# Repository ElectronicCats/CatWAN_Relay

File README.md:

# CatWAN Relay

Are you interested in applying LoRa in an industrial environment or even connect a CNC or a PLC as well to a LoRaWAN network? 

This board allows you to communicate with every LoRa device which works in the 915 Mhz band.

In this board you will find 3 relays outputs and 3 opto-isolated inputs, and it can be powered from 12v to 24v with a on/off jumper.

By now the provided firmware works as an invisible way to connect two wireless relays based on interrupts, this board its compatible with the [Arduino LoRa library](https://github.com/sandeepmistry/arduino-LoRa) from @sandeepmistry but it can work with the [Radio Head library](https://www.airspayce.com/mikem/arduino/RadioHead/) this using only the LoRa radio if you want to use LoRaWAN you should use the [Arduino LMIC](https://github.com/matthijskooijman/arduino-lmic/tree/non-avr-printf).

This device can work in networks LoRaWAN compatible with classes A, B and C, although we currently do not have a firmware for this way of working. The CatWAN Relay firmware is completely open source and you can find it in our repository along with the schematic. If you want to reprogram this device you can do it through Arduino IDE and its USB port or if you do not have to use a J-Link. ATMEL-ICE or a DIY SWD programmer

This device has a SAMD21 ARM Cortex microcontroller at 48Mhz with native USB 2.1, with 256Kb for programming, compatible with Arduino and Circuit Python.

Check [our repository](https://github.com/ElectronicCats/Arduino_Boards_Index) for Arduino IDE more details and software downloads!

Designed by Electronic Cats.
# License 

Firmware released under an GNU AGPL v3.0 license. See the LICENSE file for more information.

Hardware released under an CERN Open Hardware Licence v1.2. See the LICENSE_HARDWARE file for more information.

Electronic Cats is a registered trademark, please do not use if you sell these PCBs.

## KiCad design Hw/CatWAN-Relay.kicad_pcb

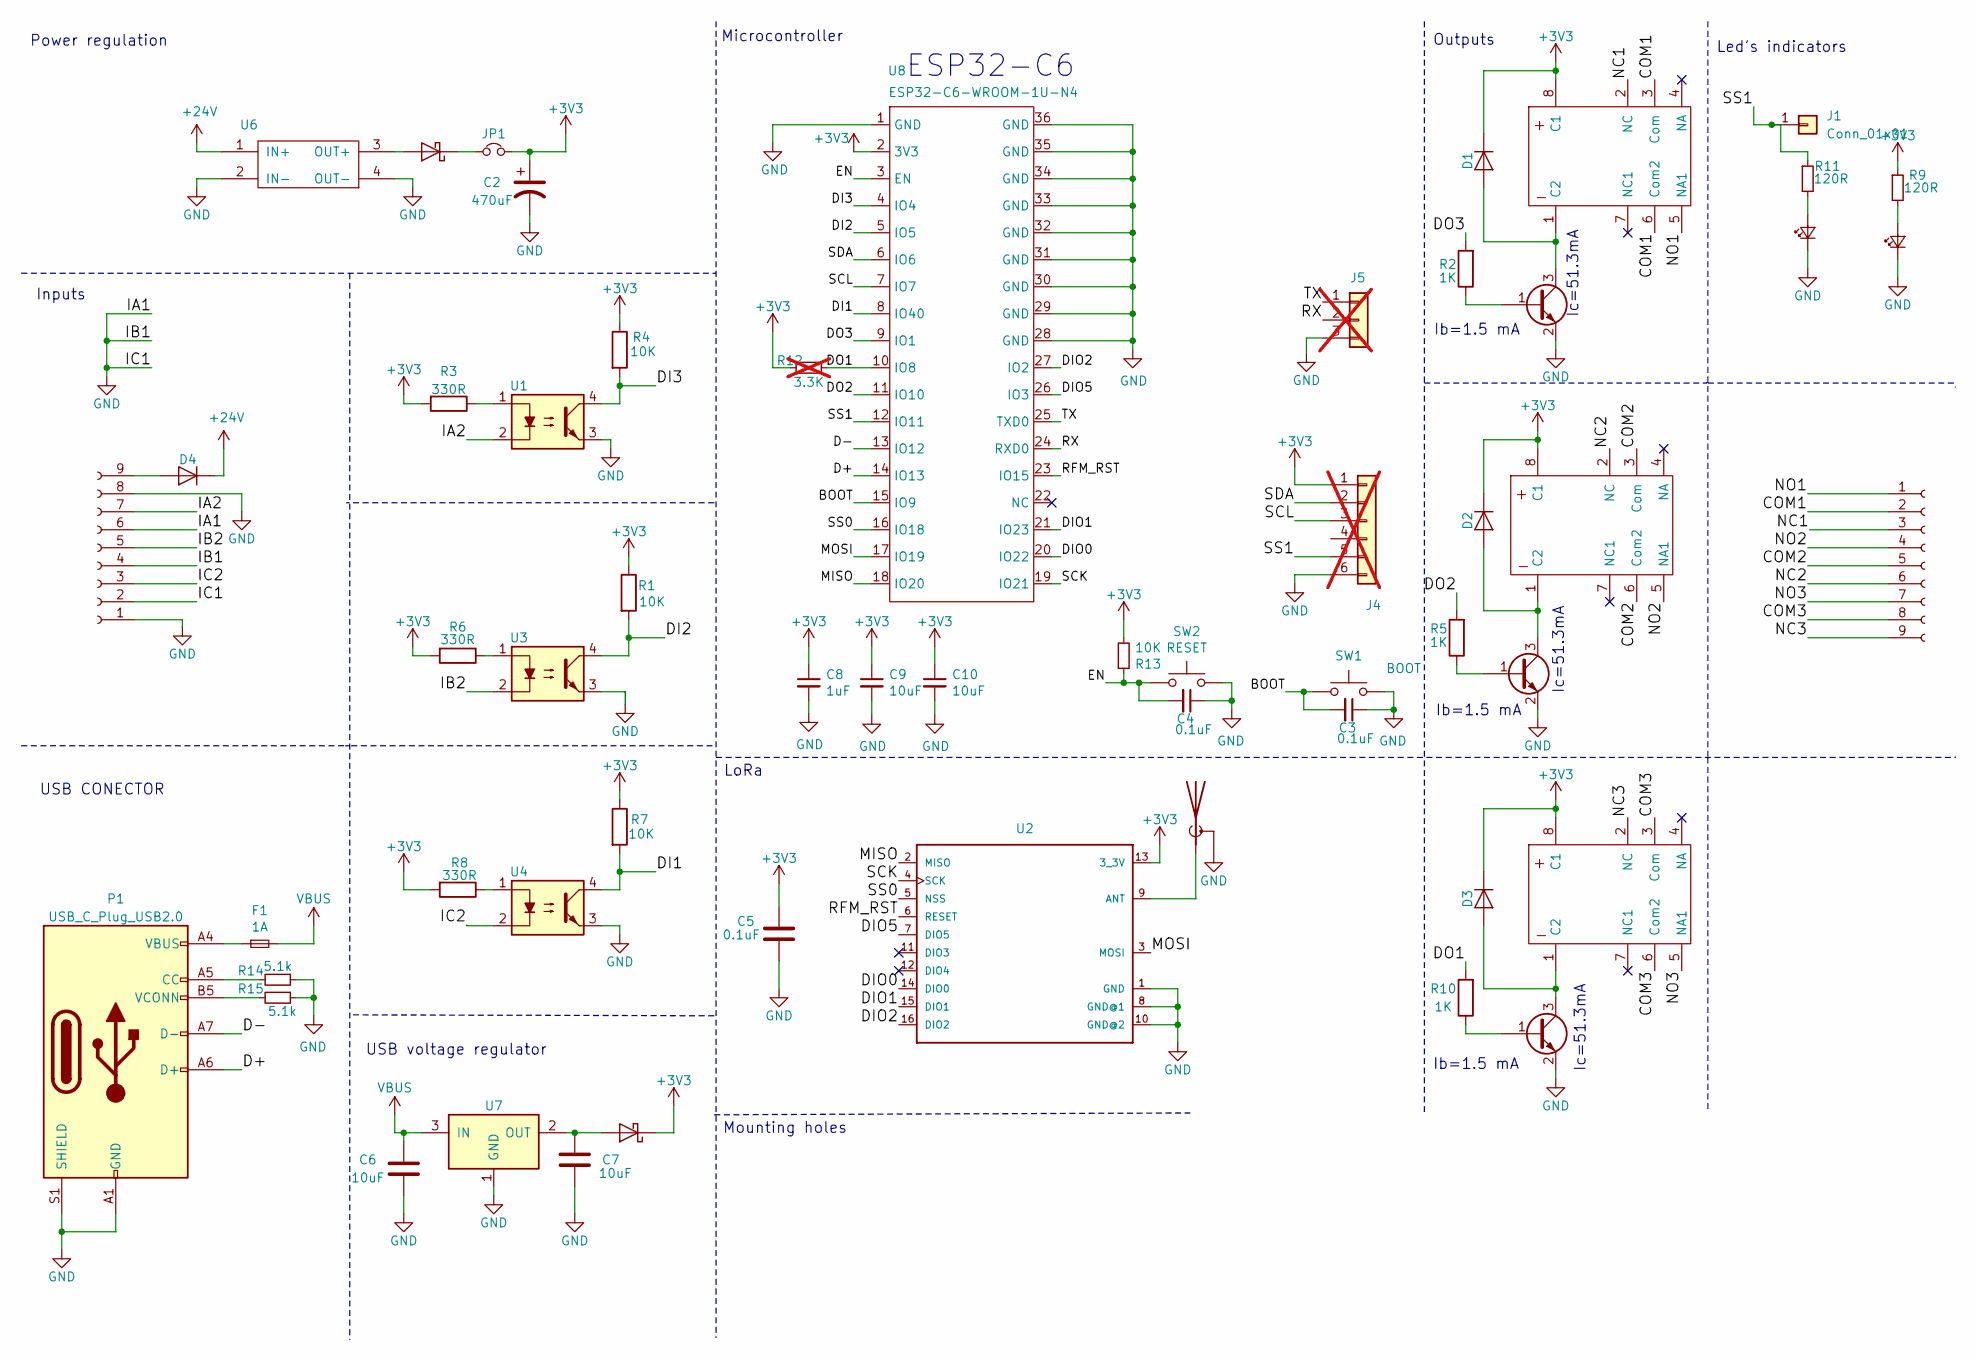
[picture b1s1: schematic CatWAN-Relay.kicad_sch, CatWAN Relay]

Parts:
AE1: Antenna_Shield; U.FL_Molex_MCRF_73412-0110_Vertical; LCSC# C7426714
C2: 470uF; C_Elec_6.3x7.7; LCSC# C5354997
C3, C4, C5: 0.1uF; C_0603_1608Metric; LCSC# C15725
C6, C7, C9, C10: 10uF; C_0603_1608Metric; LCSC# C85713
C8: 1uF; C_0603_1608Metric; LCSC# C15849
D1, D2, D3, D4: SOD4007-MS; D_SOD-123F; LCSC# C3008061
D5, D8: MBR120; D_SOD-123; LCSC# C130880
D6: ON; LED_0805_2012Metric_Pad1.15x1.40mm_HandSolder; LCSC# C130114
D7: SS0_LED; LED_0805_2012Metric_Pad1.15x1.40mm_HandSolder; LCSC# C130114
F1: 1A; Fuse_0603_1608Metric; LCSC# C151139
J1: Conn_01x01; PinHeader_1x01_P2.54mm_Vertical
J2: INPUTS; TerminalBlock_Phoenix_MKDS-1,5-9-5.08_1x09_P5.08mm_Horizont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
J3: OUTPUTS; TerminalBlock_Phoenix_MKDS-1,5-9-5.08_1x09_P5.08mm_Horizont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
J4: I2C; PinHeader_1x06_P2.54mm_Vertical; not fitted
J5: Serial; PinHeader_1x03_P2.54mm_Vertical; not fitted
JP1: ADJ; PinHeader_1x02_P2.54mm_Vertical
P1: USB_C_Plug_USB2.0; C393939; LCSC# C393939
Q1, Q2, Q3: MMBT2222A; SOT-23; LCSC# C916372
R1, R4, R7, R13: 10K; R_0603_1608Metric; LCSC# C15401
R2, R5, R10: 1K; R_0603_1608Metric; LCSC# C115325
R3, R6, R8: 330R; R_0603_1608Metric; LCSC# C25231
R9, R11: 120R; R_0603_1608Metric; LCSC# C22787
R12: 3.3K; R_0603_1608Metric; not fitted
R14, R15: 5.1k; R_0603_1608Metric; LCSC# C122969
SW1: BOOT; SW_Push_SPST_NO_Alps_SKRK; LCSC# C455281
SW2: RESET; SW_Push_SPST_NO_Alps_SKRK; LCSC# C455281
U1, U3, U4: AT3H7C-CuH-S; SOP-4_4.4x2.6mm_P1.27mm; LCSC# C20612661
U2: RFM95W-915-868; RFM95W
U6: LM2596_DC-DC; LM2596DC-DC
U7: AP2114H-3.3TRG1; SOT-223-3_TabPin2; LCSC# C150716
U8: ESP32-C6-WROOM-1U-N4; ESP32-C6-WROOM-1U
Y1, Y2, Y3: UD2-3NU; LCSC# C90259

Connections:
+3V3: C2.1, C5.1, C8.1, C9.1, C10.1, D1.1 (K), D2.1 (K), D3.1 (K), D5.1 (K), J4.1, JP1.2, R1.1, R3.2, R4.1, R6.2, R7.1, R8.2, R9.1, R12.2, R13.2, U2.13 (3_3V), U8.2 (3V3), Y1.8 (C1), Y2.8 (C1), Y3.8 (C1)
+24V: D4.1 (K), U6.1 (IN+)
/<NO NET>: J4.4
/BOOT: C3.2, SW1.2, U8.15 (IO9)
/COM1: J3.2, Y1.3 (Com), Y1.6 (Com2)
/COM2: J3.5, Y2.3 (Com), Y2.6 (Com2)
/COM3: J3.8, Y3.3 (Com), Y3.6 (Com2)
/D+: P1.A6 (D+), U8.14 (IO13)
/D-: P1.A7 (D-), U8.13 (IO12)
/DI1: R7.2, U4.4, U8.8 (IO40)
/DI2: R1.2, U3.4, U8.5 (IO5)
/DI3: R4.2, U1.4, U8.4 (IO4)
/DIO0: U2.14 (DIO0), U8.20 (IO22)
/DIO1: U2.15 (DIO1), U8.21 (IO23)
/DIO2: U2.16 (DIO2), U8.27 (IO2)
/DIO5: U2.7 (DIO5), U8.26 (IO3)
/DO1: R10.2, R12.1, U8.10 (IO8)
/DO2: R5.2, U8.11 (IO10)
/DO3: R2.2, U8.9 (IO1)
/EN: C4.2, R13.1, SW2.2, U8.3 (EN)
/IA2: J2.7, U1.2
/IB2: J2.5, U3.2
/IC2: J2.3, U4.2
/MISO: U2.2 (MISO), U8.18 (IO20)
/MOSI: U2.3 (MOSI), U8.17 (IO19)
/NC1: J3.3, Y1.2 (NC)
/NC2: J3.6, Y2.2 (NC)
/NC3: J3.9, Y3.2 (NC)
/NO1: J3.1, Y1.5 (NA1)
/NO2: J3.4, Y2.5 (NA1)
/NO3: J3.7, Y3.5 (NA1)
/RFM_RST: U2.6 (RESET), U8.23 (IO15)
/RX: J5.2, U8.24 (RXD0)
/SCK: U2.4 (SCK), U8.19 (IO21)
/SCL: J4.3, U8.7 (IO7)
/SDA: J4.2, U8.6 (IO6)
/SS0: U2.5 (NSS), U8.16 (IO18)
/SS1: J1.1, J4.5, R11.1, U8.12 (IO11)
/TX: J5.1, U8.25 (TXD0)
GND: AE1.2 (Shield), C2.2, C3.1, C4.1, C5.2, C6.2, C7.2, C8.2, C9.2, C10.2, D6.1 (K), D7.1 (K), J2.1, J2.2, J2.4, J2.6, J2.8, J4.6, J5.3, P1.A1 (GND), P1.A12 (GND), P1.B1 (GND), P1.B12 (GND), P1.S1 (SHIELD), Q1.2 (E), Q2.2 (E), Q3.2 (E), R14.1, R15.1, SW1.1, SW2.1, U1.3, U2.1 (GND), U2.8 (GND@1), U2.10 (GND@2), U3.3, U4.3, U6.2 (IN-), U6.4 (OUT-), U7.1 (GND), U8.1 (GND), U8.28 (GND), U8.29 (GND), U8.30 (GND), U8.31 (GND), U8.32 (GND), U8.33 (GND), U8.34 (GND), U8.35 (GND), U8.36 (GND), U8.37 (GND)
unnamed: AE1.1 (A), U2.9 (ANT)
unnamed: D1.2 (A), Q1.3 (C), Y1.1 (C2)
unnamed: D2.2 (A), Q2.3 (C), Y2.1 (C2)
unnamed: D3.2 (A), Q3.3 (C), Y3.1 (C2)
unnamed: D4.2 (A), J2.9
unnamed: C7.1, D5.2 (A), U7.2 (OUT)
unnamed: D6.2 (A), R9.2
unnamed: D7.2 (A), R11.2
unnamed: D8.2 (A), U6.3 (OUT+)
unnamed: D8.1 (K), JP1.1
unnamed: F1.1, P1.A4 (VBUS), P1.A9 (VBUS), P1.B4 (VBUS), P1.B9 (VBUS)
unnamed: P1.A5 (CC), R14.2
unnamed: P1.B5 (VCONN), R15.2
unnamed: Q1.1 (B), R2.1
unnamed: Q2.1 (B), R5.1
unnamed: Q3.1 (B), R10.1
unnamed: R3.1, U1.1
unnamed: R6.1, U3.1
unnamed: R8.1, U4.1
VBUS: C6.1, F1.2, U7.3 (IN)

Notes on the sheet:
LoRa
Inputs
Microcontroller
Ic=51.3mA
USB voltage regulator
USB CONECTOR
Power regulation
Mounting holes
ESP32-C6
Ib=1.5 mA
Led's indicators
Outputs

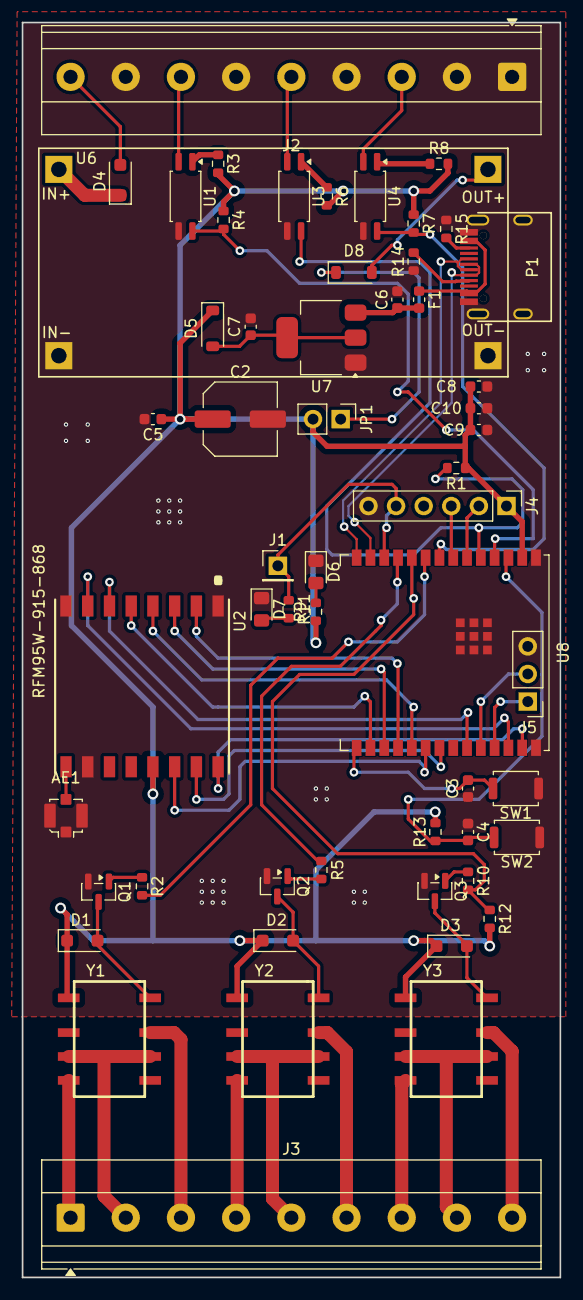
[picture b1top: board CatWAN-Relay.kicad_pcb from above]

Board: 2 copper layers, 49.5 x 115.5 mm, 56 parts (0 on the bottom side), 59 nets.

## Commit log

2018-08-22 Add gitignore
2018-08-22 Add KiCAD project
2018-08-22 Add Fw
2018-12-19 Add schematic PDF
2019-05-22 Add possible pcb dimmensions
2019-05-23 add measures
2019-09-06 First route
2020-02-25 Update example
2020-10-13 Add_Diode
2020-10-18 update labels and logos
2020-10-18 SWD SMD and fix labels
2022-04-26 add serial control for relays
2022-04-26 update project to kicad6
2022-09-13 remove squematic oldversion
2022-10-19 Update BOM
2024-10-26 feat: init CatWan relay 2
2024-11-01 feat(Hw):Update_sch_aadded_footprints_symbols
2024-11-05 fix: labels tx, rx and rx_leds
2024-11-05 feat(hw): USB C schematic changed & fusible added & references added
2024-11-06 feat: UPDATE BOM & diode changed
2024-11-06 fix: label RX led
2024-11-07 feat(hw): Footprint added
2024-11-07 feat(hw): Change optocoupler and D1-D4 mfr# and update footprints
2024-11-07 feat(hw): Update ESP32-C6 and RFM95 mfr.#
2024-11-07 feat: components placed
2024-11-08 feat: Boot and Reset buttons footprint changed
2024-11-08 Feat: floorplan added
2024-12-11 feat(Hw):First_Route_v2
2024-12-19 feat: add zone with no fill
2024-12-19 feat: change routes width
2024-12-19 fix: move labels
2024-12-26 feat(hw): add labels in PCB design
2025-01-08 feat(Hw):Update_Tracks
2025-01-08 feat(Hw):added_labels
2025-11-05 feat: init project NFC
2025-11-05 feat: assign card with relay
2025-11-05 docs: update README
2025-11-05 feat: change name for IDdevice
2026-01-23 files_modified, READEME, .ino, .h, .cpp files_added, .h, .cpp
2026-01-30 feat: files_modified, .ino.h, .cpp, README
2026-01-30 feat: add, WiFi_ERROR
2026-01-30 feat: fix README_WIFI_ERROR
2026-01-30 feat: fix ESP32 NFC to Google, add get time
2026-02-05 feat: files_modified, _pro, _pcb & _sch
2026-02-05 feat: fix pcb
2026-03-02 Feat: bugs fixed
